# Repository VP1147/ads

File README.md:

## Arduino microcontroler code for ADS (Atmospheric Deposition Sampler).

Instructions, circuits and documentation are avaliable on https://github.com/vp1147/ads.  

### Copyright and License

This code is under MIT License (See LICENSE for more information).  

Copyright (c) 2022 *Vinícius Pavão*  

LCA (Atmospheric Sciences Laboratory),
INFI (Institute of Physics),
UFMS (Federal University of Mato Grosso do Sul).

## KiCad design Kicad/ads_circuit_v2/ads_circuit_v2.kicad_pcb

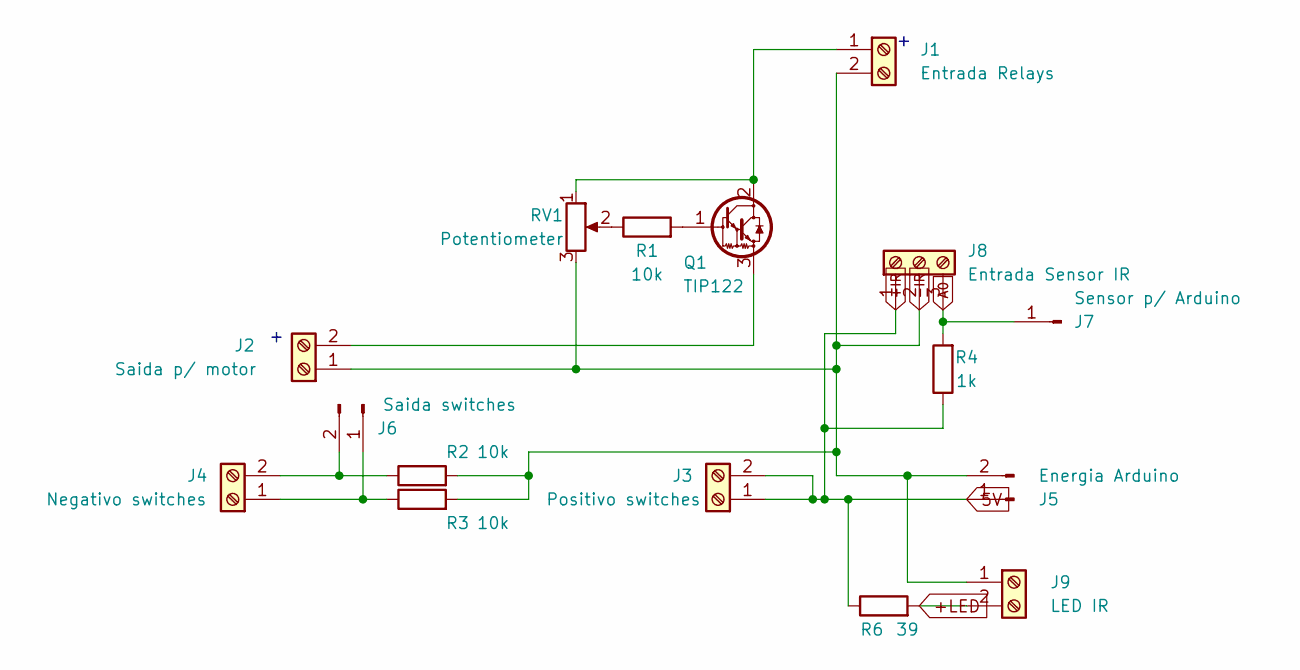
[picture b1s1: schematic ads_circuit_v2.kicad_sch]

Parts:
J1: Entrada Relays; TerminalBlock_RND_205-00001_1x02_P5.00mm_Horizontal
J2: Saida p/ motor; TerminalBlock_RND_205-00001_1x02_P5.00mm_Horizontal
J3: Positivo switches; TerminalBlock_RND_205-00001_1x02_P5.00mm_Horizontal
J4: Negativo switches; TerminalBlock_RND_205-00001_1x02_P5.00mm_Horizontal
J5: Energia Arduino; PinHeader_1x02_P1.27mm_Vertical
J6: Saida switches; PinHeader_1x02_P1.27mm_Vertical
J7: Sensor p/ Arduino; PinHeader_1x01_P1.27mm_Vertical
J8: Entrada Sensor IR; TerminalBlock_RND_205-00002_1x03_P5.00mm_Horizontal
J9: LED IR; TerminalBlock_RND_205-00001_1x02_P5.00mm_Horizontal
Q1: TIP122; TO-220-3_Vertical
R1, R2, R3: 10k; R_Axial_DIN0207_L6.3mm_D2.5mm_P10.16mm_Horizontal
R4: 1k; R_Axial_DIN0207_L6.3mm_D2.5mm_P10.16mm_Horizontal
R6: 39; R_Axial_DIN0207_L6.3mm_D2.5mm_P10.16mm_Horizontal
RV1: Potentiometer; Potentiometer_Alps_RK163_Single_Horizontal

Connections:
5V: J3.1, J3.2, J5.1, J8.1, R4.1, R6.1
+LED: J9.2, R6.2
-IR: J1.2, J2.1, J5.2, J8.2, J9.1, R2.2, R3.2, RV1.3
A0: J7.1, J8.3, R4.2
unnamed: J1.1, Q1.2 (C), RV1.1
unnamed: J2.2, Q1.3 (E)
unnamed: J4.1, J6.1, R3.1
unnamed: J4.2, J6.2, R2.1
unnamed: Q1.1 (B), R1.2
unnamed: R1.1, RV1.2

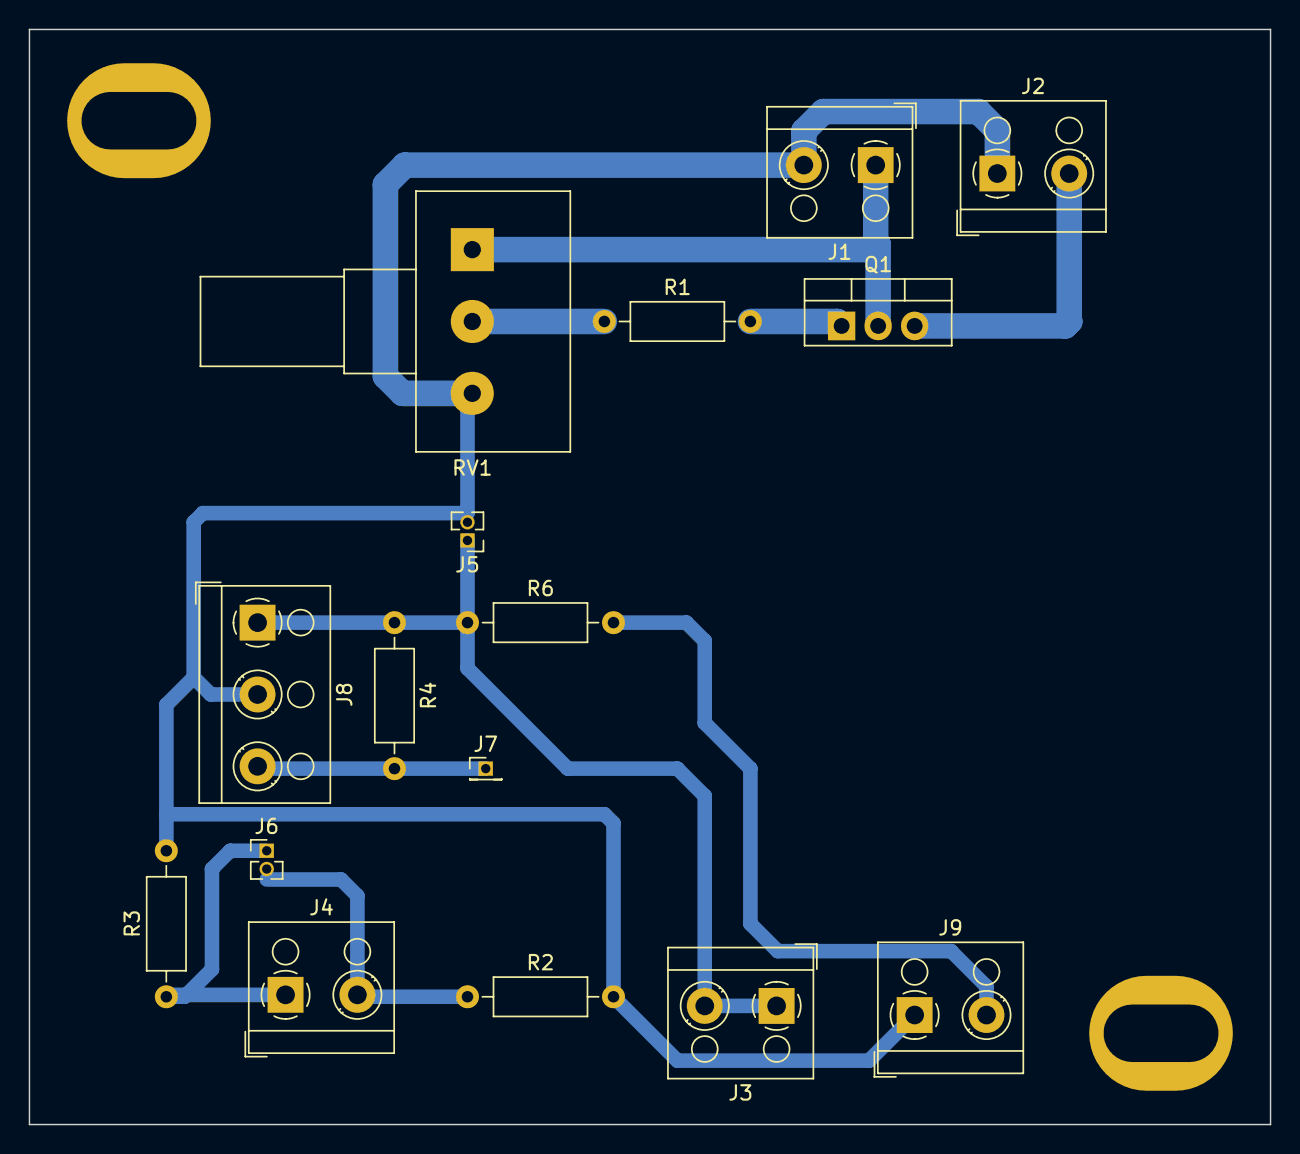
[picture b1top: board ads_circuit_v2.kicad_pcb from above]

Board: 2 copper layers, 86.4 x 76.2 mm, 16 parts (0 on the bottom side), 10 nets.

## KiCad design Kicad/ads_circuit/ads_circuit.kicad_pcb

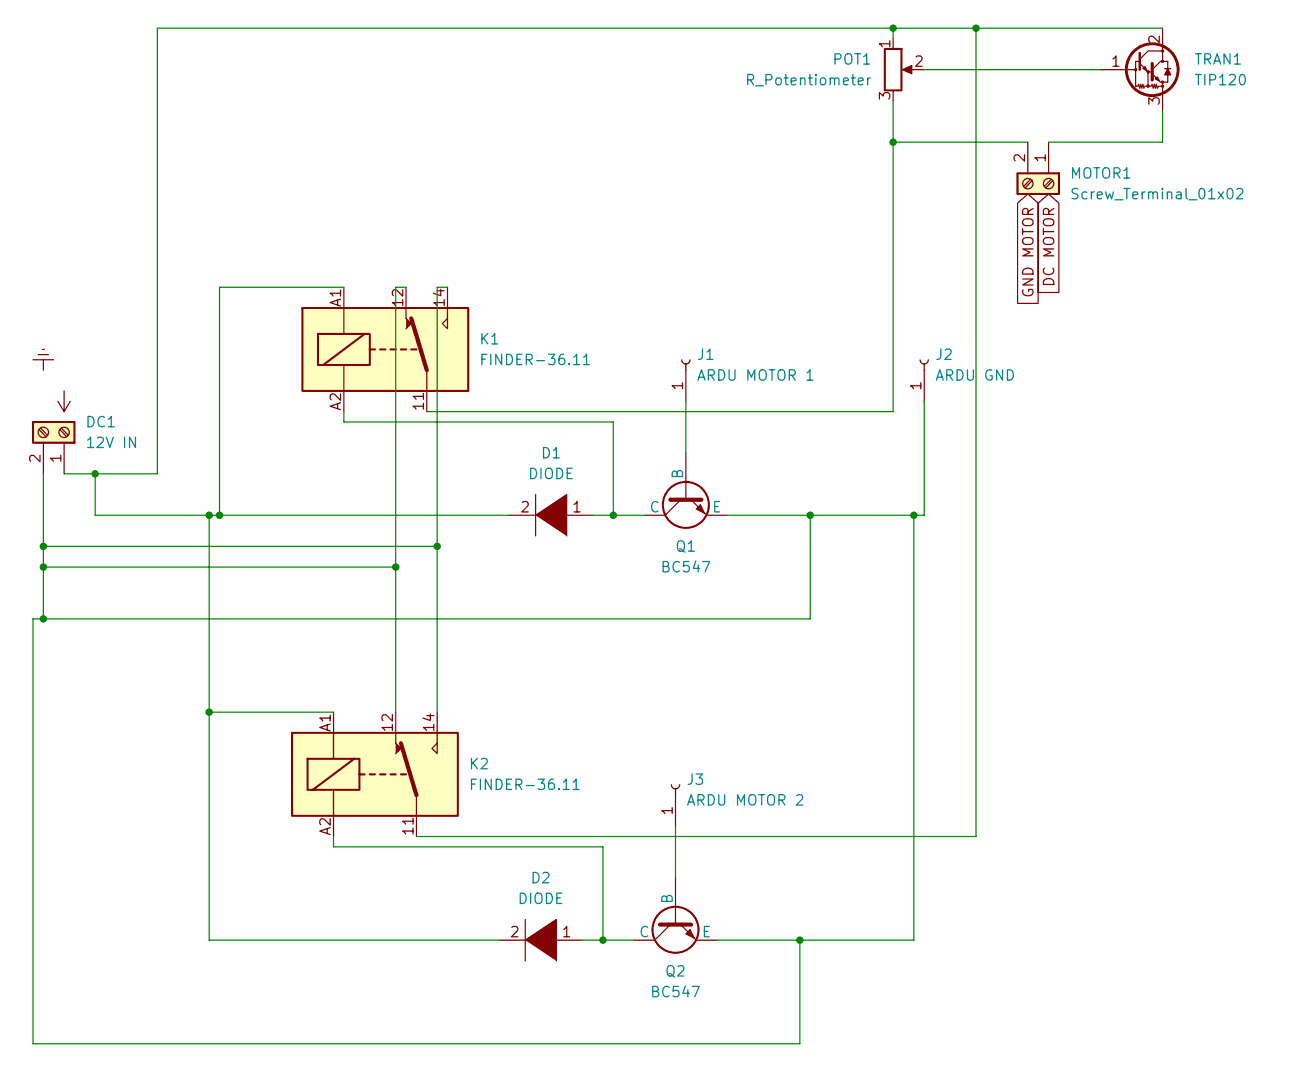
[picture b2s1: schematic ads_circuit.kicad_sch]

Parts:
D1, D2: DIODE; D_A-405_P7.62mm_Horizontal
DC1: 12V IN; TerminalBlock_RND_205-00001_1x02_P5.00mm_Horizontal
J1: ARDU MOTOR 1; PinHeader_1x01_P1.00mm_Vertical
J2: ARDU GND; PinHeader_1x01_P1.00mm_Vertical
J3: ARDU MOTOR 2; PinHeader_1x01_P1.00mm_Vertical
K1, K2: FINDER-36.11; Relay_SPDT_Finder_36.11
MOTOR1: Screw_Terminal_01x02; TerminalBlock_RND_205-00001_1x02_P5.00mm_Horizontal
POT1: R_Potentiometer; Potentiometer_Piher_T-16H_Single_Horizontal
Q1, Q2: BC547; TO-92_Inline
TRAN1: TIP120; TO-220-3_Vertical

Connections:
unnamed: D1.1 (K), K1.A2, Q1.1 (C)
unnamed: D1.2 (A), D2.2 (A), DC1.1, K1.A1, K2.11, K2.A1, POT1.1, TRAN1.2 (C)
unnamed: D2.1 (K), K2.A2, Q2.1 (C)
unnamed: DC1.2, J2.1, K1.12, K1.14, K2.12, K2.14, Q1.3 (E), Q2.3 (E)
unnamed: J1.1, Q1.2 (B)
unnamed: J3.1, Q2.2 (B)
unnamed: K1.11, MOTOR1.2, POT1.3
unnamed: MOTOR1.1, TRAN1.3 (E)
unnamed: POT1.2, TRAN1.1 (B)

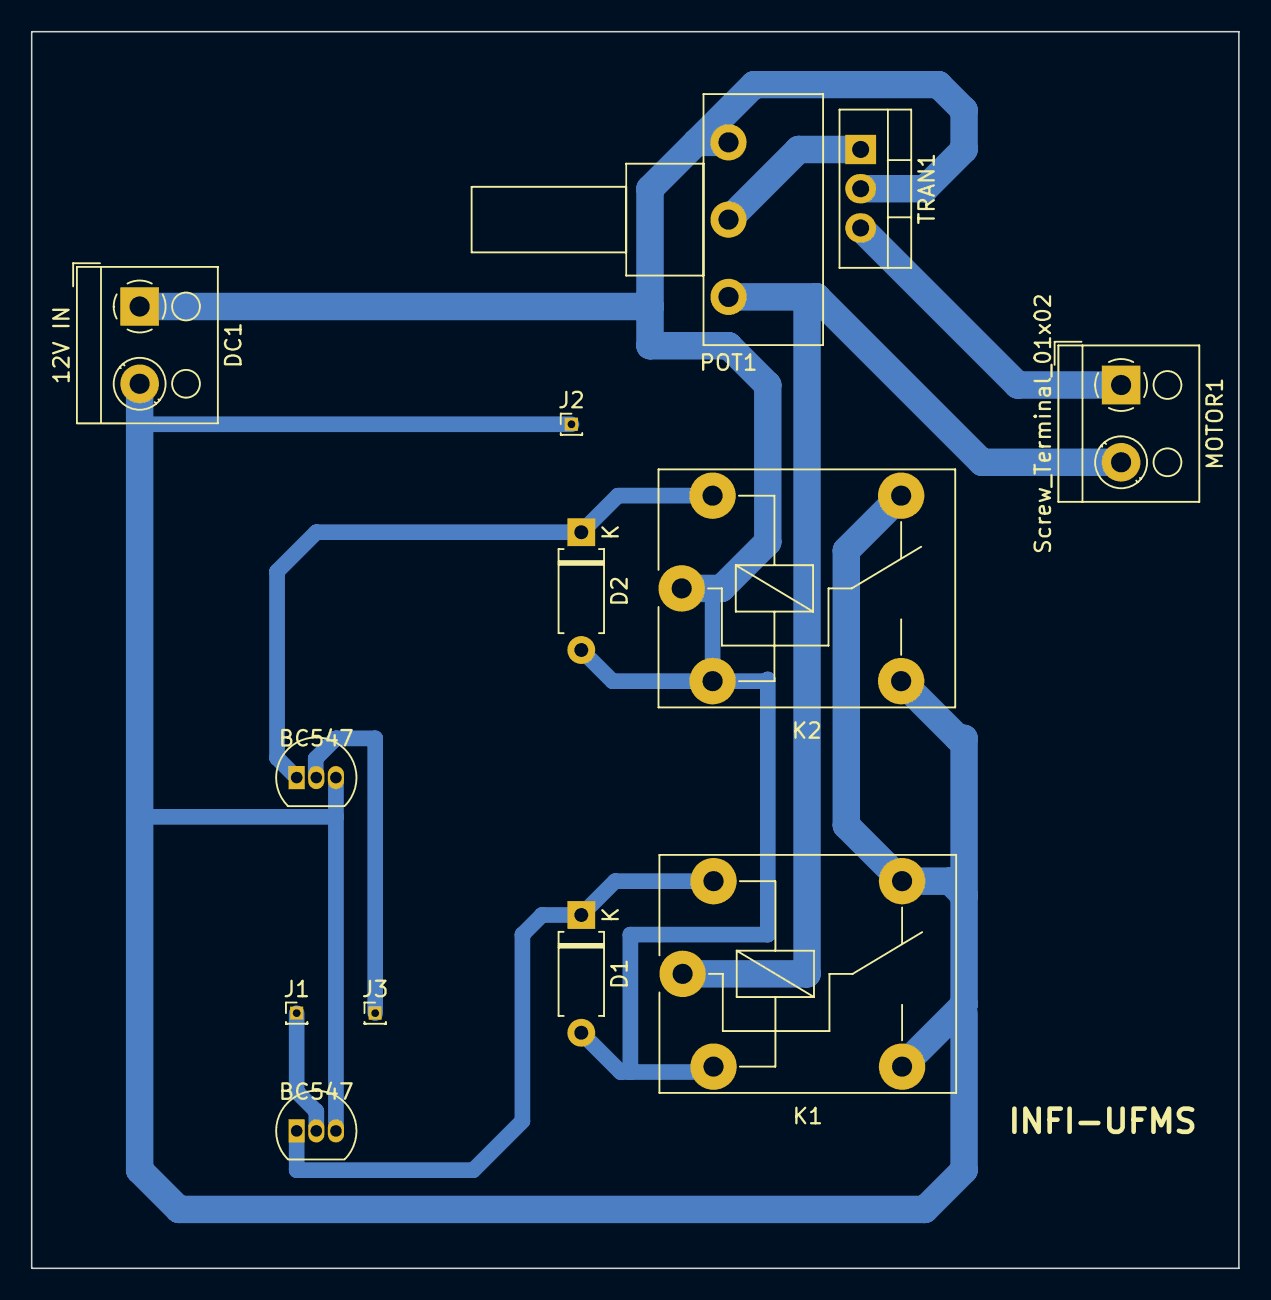
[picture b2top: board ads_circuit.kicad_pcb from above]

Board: 2 copper layers, 78.1 x 80.0 mm, 13 parts (0 on the bottom side), 9 nets.

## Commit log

2022-11-07 Created open() and close() functions
2022-11-29 Descriptions
2022-12-12 Updated scheme
2023-01-11 Debug variables
2023-02-04 Motor control and commands
2023-02-22 Minor corrections
2023-12-06 Update scheme
2024-02-02 Update circuit
2024-04-23 Kicad scheme
2024-09-20 Update KiCAD scheme
2024-09-20 Added information LEDs
2025-02-25 Updated Kicad model
